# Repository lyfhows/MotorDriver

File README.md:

# L298N Dual Motor Driver with Power Monitoring

A custom KiCad PCB built around the **L298N** dual H-bridge. It improves on the common red L298N module with Schottky flyback diodes, reverse-polarity and surge protection, an onboard logic supply, voltage / current / power monitoring over I2C, and a hardware overcurrent limit that works without firmware.

---

## Features

- Drives **two independent brushed DC motors** (or one motor with both channels paralleled)
- **Schottky flyback diodes** (SS36) on all four outputs, instead of the slow 1N4007s on stock modules
- **Three INA226 monitors** over I2C:
  - supply voltage, total current and power
  - current of motor A
  - current of motor B
- **Hardware overcurrent limit** (LM393 comparators) that cuts the enable lines with no firmware involved
- **Input protection:** fuse, reverse-polarity P-MOSFET, TVS surge diode and a gate-clamp zener
- **Onboard logic supply:** 5 V buck converter (AP63205) plus a 3.3 V LDO
- **3.3 V or 5 V logic** selectable with a solder jumper, so it works with ESP32 / Pico / STM32 or 5 V Arduino boards
- **Pull-down and series resistors** on all control inputs, so the motors stay off while the MCU is unpowered or booting
- Hand-solderable parts (no BGA, no leadless packages)

## Specifications

| Item | Value |
|---|---|
| Motor driver | L298N, Multiwatt15 |
| Supply voltage | Mostly 12 V or below, designed for up to **24 V** |
| Motor current | 2 A continuous per channel, about 2.5 A repetitive peak, about 4 A total |
| Input path rating | Sized for **5 A** as headroom (fuse 6.3 A). This is not an expected load. |
| Voltage drop | The L298N's bipolar bridge drops roughly 2 to 4 V, so at 12 V a motor sees about 9 V |
| Logic level | 3.3 V or 5 V, set by SJ1 |
| Speed control | PWM on ENA / ENB |
| Direction control | IN1 to IN4 |
| Overcurrent limit | About 2.3 A per channel (adjustable with RV1), hiccup behaviour |
| Monitoring | 3 × INA226 at I2C addresses 0x40, 0x41, 0x42 |
| Board | 110 × 90 mm, 2 layers, 2 oz copper |
| Assembly | Hand soldering |

## Block diagram

```mermaid
flowchart LR
  BAT[Battery] --> F1[Fuse F1]
  F1 --> Q1[Reverse-polarity MOSFET Q1]
  Q1 --> RS1[Shunt RS1 with INA226 U2]
  RS1 --> VS[Motor supply rail VS]
  VS --> U1[L298N U1]
  U1 --> MA[Motor A]
  U1 --> MB[Motor B]
  VS --> U3[5 V buck U3]
  U3 --> U5[3.3 V LDO U5]
  U3 --> SJ1[Logic rail selector SJ1]
  U5 --> SJ1
  SJ1 --> MON[INA226s, LM393, I2C pull-ups]
  U1 -- SENSE pins --> SH[Shunts RSA and RSB]
  SH --> I6[INA226 U6 and U7]
  SH --> CMP[LM393 comparator U4]
  CMP -- pulls enable low --> U1
  MCU[Microcontroller] -- PWM and direction --> U1
  MCU <-- I2C --> MON
```

## How it works

### Power path
Battery positive goes through the fuse (F1) and the P-channel MOSFET (Q1), which blocks reverse polarity. It then passes through the 15 mΩ shunt (RS1), which the first INA226 (U2) measures, and arrives at the motor supply rail. The TVS diode (D11) and 470 µF bulk capacitor (C1) sit on that rail, which feeds the L298N's VS pin and the buck converter.

### Logic power
The AP63205 buck converter makes 5 V from the supply rail. A 3.3 V LDO (AP2112K-3.3) follows it. The solder jumper **SJ1** chooses which of the two feeds the "logic rail", which powers the INA226s, the LM393 and the I2C pull-ups. Bridge it to match your microcontroller's logic level. The L298N's logic supply pin always runs from 5 V.

### Current monitoring
- **U2** measures the total current drawn from the supply across the 15 mΩ shunt RS1, plus the supply voltage and power.
- **U6** and **U7** measure each motor's current across a 33 mΩ shunt (RSA, RSB) connected to the L298N's SENSE pins.
- Each INA226 has 10 Ω input filter resistors and a 100 nF capacitor across its inputs.

### Hardware overcurrent limit
Each SENSE voltage also goes through a 1 kΩ / 100 nF filter to a comparator in the LM393 (U4). A trimmer (RV1) sets the reference to about 75 mV, which is roughly 2.3 A on a 33 mΩ shunt. When the current exceeds that, the comparator's open-collector output pulls the matching enable line low through a BAT54J Schottky diode, and the motor current falls. The limit is **not latched**: the motor restarts when the current drops, so a stalled motor pulses on and off.

### Input protection for control lines
IN1 to IN4 have 100 Ω series resistors and 10 kΩ pull-downs. ENA and ENB have 2.2 kΩ series resistors and 22 kΩ pull-downs. With the MCU off or disconnected, the bridge stays disabled.

## Bill of materials

**ICs and semiconductors**

| Ref | Part | Footprint |
|---|---|---|
| U1 | L298N (Multiwatt15) | `Package_TO_SOT_THT:TO-220-15_P2.54x2.54mm_StaggerOdd_Lead4.58mm_Vertical` |
| U2, U6, U7 | INA226AIDGSR | `Package_SO:VSSOP-10_3x3mm_P0.5mm` |
| U3 | AP63205WU-7 (5 V buck) | `Package_TO_SOT_SMD:TSOT-23-6` |
| U4 | LM393 (dual comparator) | `Package_SO:SOIC-8_3.9x4.9mm_P1.27mm` |
| U5 | AP2112K-3.3 (3.3 V LDO) | `Package_TO_SOT_SMD:SOT-23-5` |
| Q1 | P-MOSFET, 40 V, at least 10 A (e.g. AOD4185) | `Package_TO_SOT_SMD:TO-252-2` |
| D1 to D8 | SS36 (60 V, 3 A Schottky) | `Diode_SMD:D_SMA` |
| D9 | LED, green (power) | `LED_SMD:LED_0805_2012Metric` |
| D10 | BZT52B15 (15 V zener) | `Diode_SMD:D_SOD-123F` |
| D11 | SMAJ28A (unidirectional TVS) | `Diode_SMD:D_SMA` |
| D12, D13 | BAT54J (Schottky) | `Diode_SMD:D_SOD-323F` |

**Resistors** (0603 unless noted)

| Ref | Value | Purpose |
|---|---|---|
| R1 to R4 | 10 kΩ | Pull-downs on IN1 to IN4 |
| R5, R6 | 22 kΩ | Pull-downs on ENA / ENB |
| R7, R8 | 2.2 kΩ | Series on ENA / ENB |
| R9 | 10 kΩ | Q1 gate to GND |
| R10, R11 | 4.7 kΩ | SDA / SCL pull-ups |
| R12 | 10 kΩ | ALERT pull-up |
| R13 | 1 kΩ | Power LED |
| R14 | 47 kΩ | Comparator reference, top |
| R15, R16 | 1 kΩ | Comparator input filters |
| R17 | 100 kΩ | Buck EN pull-up |
| R18 to R21 | 100 Ω | Series on IN1 to IN4 |
| R22 to R27 | 10 Ω | INA226 input filters |
| RS1 | 15 mΩ, 1 W, 1%, 2512 | Supply shunt |
| RSA, RSB | 33 mΩ, 1 W, 1%, 2512 | Motor shunts |
| RV1 | 2 kΩ multiturn trimmer | Trip threshold (Bourns 3296W) |

**Capacitors**

| Ref | Value | Footprint |
|---|---|---|
| C1 | 470 µF, 50 V electrolytic | `Capacitor_THT:CP_Radial_D10.0mm_P5.00mm` |
| C5 | 10 µF, 50 V | `Capacitor_SMD:C_1206_3216Metric` |
| C6 | 22 µF, 16 V | `Capacitor_SMD:C_1206_3216Metric` |
| C8 | 1 µF | `Capacitor_SMD:C_0805_2012Metric` |
| C9 | 2.2 µF | `Capacitor_SMD:C_0805_2012Metric` |
| C2 to C4, C7, C10 to C18 | 100 nF, 50 V X7R | `Capacitor_SMD:C_0805_2012Metric` |

Ceramic capacitors lose capacitance under DC bias, so keep C5 and C6 in 1206 or larger.

**Other parts**

| Ref | Part | Notes |
|---|---|---|
| L1 | 4.7 µH shielded inductor, saturation current 3 A or more | The AP63205 datasheet recommends 4.7 µH for a 5 V output. Confirm against your datasheet. |
| F1 | 6.3 A fast-blow fuse, 5×20 mm, with PCB holder | |
| SJ1 | 3-pad solder jumper | Selects 5 V or 3.3 V logic |
| JP1, JP2 | 2-pad solder jumpers, bridged | Disconnect the I2C pull-ups if needed |
| J1 to J3 | 2-pin 5.08 mm screw terminals | Battery, motor A, motor B |
| J4 | 1×7 pin header | Control inputs |
| J5 | 1×5 pin header | I2C and alert |
| H1 to H4 | M3 mounting holes | Unplated, no electrical connection |
| TP1 to TP8 | Test points | |
| HS1 | Heatsink with thermal pad | Not on the PCB. Mounts on the L298N tab. |

**Totals:** 80 components, or 92 footprints including the mounting holes and test points. You also need to buy the fuse, the heatsink and an M3 screw for the L298N tab.

## Connector pinouts

| Connector | Pin | Signal |
|---|---|---|
| **J1** battery | 1 | Battery positive |
| | 2 | GND |
| **J2** motor A | 1, 2 | OUT1, OUT2 |
| **J3** motor B | 1, 2 | OUT3, OUT4 |
| **J4** control | 1 | ENA |
| | 2 to 5 | IN1, IN2, IN3, IN4 |
| | 6 | ENB |
| | 7 | GND |
| **J5** I2C | 1 | SDA |
| | 2 | SCL |
| | 3 | ALERT |
| | 4 | Logic rail output (3.3 V or 5 V, as set by SJ1) |
| | 5 | GND |

**SJ1:** pin 1 is +5 V, pin 3 is +3.3 V, and pin 2 (the centre pad) is the logic rail. Solder-bridge pins 1 and 2 for 5 V logic, or pins 2 and 3 for 3.3 V logic. Never bridge all three. Don't back-feed the logic rail from the MCU.

### L298N pin connections

| Pin | Signal |
|---|---|
| 1 | SENSE_A (to RSA, then GND) |
| 2, 3 | OUT1, OUT2 |
| 4 | VS (motor supply) |
| 5, 7 | IN1, IN2 |
| 6 | ENA |
| 8 | GND (the metal tab is also GND) |
| 9 | VSS (+5 V logic) |
| 10, 12 | IN3, IN4 |
| 11 | ENB |
| 13, 14 | OUT3, OUT4 |
| 15 | SENSE_B (to RSB, then GND) |

**Flyback diodes:** D1, D2, D5 and D6 go from OUT1, OUT2, OUT3 and OUT4 up to VS (anode on the output). D3, D4, D7 and D8 go from GND to OUT1, OUT2, OUT3 and OUT4 (anode on GND).

### INA226 pin connections (VSSOP-10)

| Pin | Name | U2 (supply, 0x40) | U6 (motor A, 0x41) | U7 (motor B, 0x42) |
|---|---|---|---|---|
| 1 | A1 | GND | GND | GND |
| 2 | A0 | GND | Logic rail | SDA |
| 3 | ALERT | ALERT | ALERT | ALERT |
| 4 | SDA | SDA | SDA | SDA |
| 5 | SCL | SCL | SCL | SCL |
| 6 | VS | Logic rail | Logic rail | Logic rail |
| 7 | GND | GND | GND | GND |
| 8 | VBUS | Motor supply rail | Same net as pin 9 | Same net as pin 9 |
| 9 | VIN− | Via R23 to the load side of RS1 | Via R25 to RSA's ground end | Via R27 to RSB's ground end |
| 10 | VIN+ | Via R22 to the battery side of RS1 | Via R24 to the SENSE_A pin | Via R26 to the SENSE_B pin |

The bus-voltage reading on U6 and U7 is meaningless (they see only millivolts), so ignore it.

## Schematic Layout

## PCB layout

## PCB 3D view

### Layout rules used

| Item | Value |
|---|---|
| Copper | 2 oz, 2 layers |
| Power tracks (VS, GND) | 2 mm or wider, or copper pours |
| Motor output tracks | 1.5 mm or wider |
| Signal tracks | 0.25 to 0.3 mm |
| Clearance | 0.3 mm or more (check your fab's minimum) |
| Part spacing | About 2 mm, for hand soldering |
| Mounting holes | 5 mm copper-free clearance |

## Bring-up procedure

1. **Check for shorts** with a multimeter (VS to GND, +5 V to GND) before applying power.
2. **Populate the power section first:** fuse, Q1, RS1, the buck and the LDO. Power it from a **current-limited bench supply** at about 12 V with the limit near 0.2 A. Confirm +5 V and +3.3 V.
3. **Solder jumper:** bridge SJ1 to match your MCU.
4. **Add the L298N and diodes.** Test with no motor, then a small motor at low PWM.
5. **Add the INA226s one at a time,** scan the I2C bus, and compare the readings against a multimeter.
6. **Set the overcurrent trimmer last:** adjust RV1 while measuring the reference voltage (about 75 mV).

## Firmware notes

### I2C addresses

| Device | Address | Measures |
|---|---|---|
| U2 | 0x40 | Supply voltage, total current, power |
| U6 | 0x41 | Motor A current |
| U7 | 0x42 | Motor B current |

### Calibration

The INA226 calibration register value is `CAL = 0.00512 / (Current_LSB × R_shunt)`.

| Chip | Shunt | Current_LSB | CAL | Full-scale |
|---|---|---|---|---|
| U2 | 15 mΩ | 1 mA | 341 | About 5.4 A |
| U6, U7 | 33 mΩ | 0.5 mA | 310 | About 2.48 A (readings saturate here) |

The power register's LSB is 25 times the Current_LSB. The bus voltage LSB is 1.25 mV.

### Minimal example (Arduino-style)

```cpp
#include <Wire.h>

const uint8_t INA_SUPPLY  = 0x40;
const uint8_t INA_MOTOR_A = 0x41;
const uint8_t INA_MOTOR_B = 0x42;

void writeReg(uint8_t addr, uint8_t reg, uint16_t val) {
  Wire.beginTransmission(addr);
  Wire.write(reg);
  Wire.write(val >> 8);
  Wire.write(val & 0xFF);
  Wire.endTransmission();
}

int16_t readReg(uint8_t addr, uint8_t reg) {
  Wire.beginTransmission(addr);
  Wire.write(reg);
  Wire.endTransmission(false);
  Wire.requestFrom(addr, (uint8_t)2);
  return (Wire.read() << 8) | Wire.read();
}

void setup() {
  Serial.begin(115200);
  Wire.begin();
  // Configuration register (0x00): 64 averages, 1.1 ms conversion time
  writeReg(INA_SUPPLY,  0x00, 0x4727);
  writeReg(INA_MOTOR_A, 0x00, 0x4727);
  writeReg(INA_MOTOR_B, 0x00, 0x4727);
  // Calibration register (0x05)
  writeReg(INA_SUPPLY,  0x05, 341);
  writeReg(INA_MOTOR_A, 0x05, 310);
  writeReg(INA_MOTOR_B, 0x05, 310);
}

void loop() {
  float busV   = readReg(INA_SUPPLY, 0x02) * 1.25 / 1000.0;  // volts
  float supplyA = readReg(INA_SUPPLY,  0x04) * 1.0 / 1000.0; // amps
  float motorA  = readReg(INA_MOTOR_A, 0x04) * 0.5 / 1000.0; // amps
  float motorB  = readReg(INA_MOTOR_B, 0x04) * 0.5 / 1000.0; // amps
  Serial.printf("V=%.2f  I_total=%.3f  I_A=%.3f  I_B=%.3f\n",
                busV, supplyA, motorA, motorB);
  delay(200);
}
```

Set the undervoltage alert limit in U2's mask/enable and alert-limit registers to suit your battery chemistry.

## Known limitations

- **The L298N can't deliver 5 A.** The 5 A figure only sizes the input path. Real limits are 2 A per channel and about 4 A in total.
- **Voltage drop:** the L298N's bipolar bridge drops roughly 2 to 4 V, and at full load it dissipates several watts and needs a heatsink (about 3 °C/W or better for continuous use).
- **Overcurrent limit is a hiccup, not a latch.** A stalled motor pulses on and off, and the MCU isn't told when it trips.
- **No short-circuit protection on the motor outputs** beyond the fuse and the hiccup limit. The L298N has no fault flag.
- **Per-motor current readings under PWM** reflect only the on-time current. The motor's freewheeling current flows through the flyback diodes and doesn't pass the shunt, so the reading is lower than the smoothed motor current. Treat it as a trend or overload indicator.
- **INA226 bus voltage rating:** VBUS has a 40 V absolute maximum. The SMAJ28A TVS clamps at about 45 V at its full surge current, so only an extreme surge could exceed it. For a supply near 24 V, consider the SMAJ26A instead.
- **No isolation** between the motor side and the logic side. They share one ground.
- **No onboard temperature sensing or fan control.**
- **Hardest part to hand-solder:** the three VSSOP-10 INA226 chips.
- **Not yet built or tested.**

## Design decisions

| Decision | Choice |
|---|---|
| Driver IC | Keep the L298N (not replaced by a MOSFET bridge) |
| Flyback diodes | Schottky SS36 instead of 1N4007 |
| Logic-side isolation | None. Series and pull-down resistors only. |
| Overcurrent protection | Comparator hiccup limit, no latch |
| Temperature sensor and fan | Left out to keep the board simple |
| Per-motor monitoring | Kept (one INA226 per motor) |
| Analog hardware P-loop | Not included. Closed-loop control is left to firmware. |

## License

MIT License

## Author

Abhinav Pentyala

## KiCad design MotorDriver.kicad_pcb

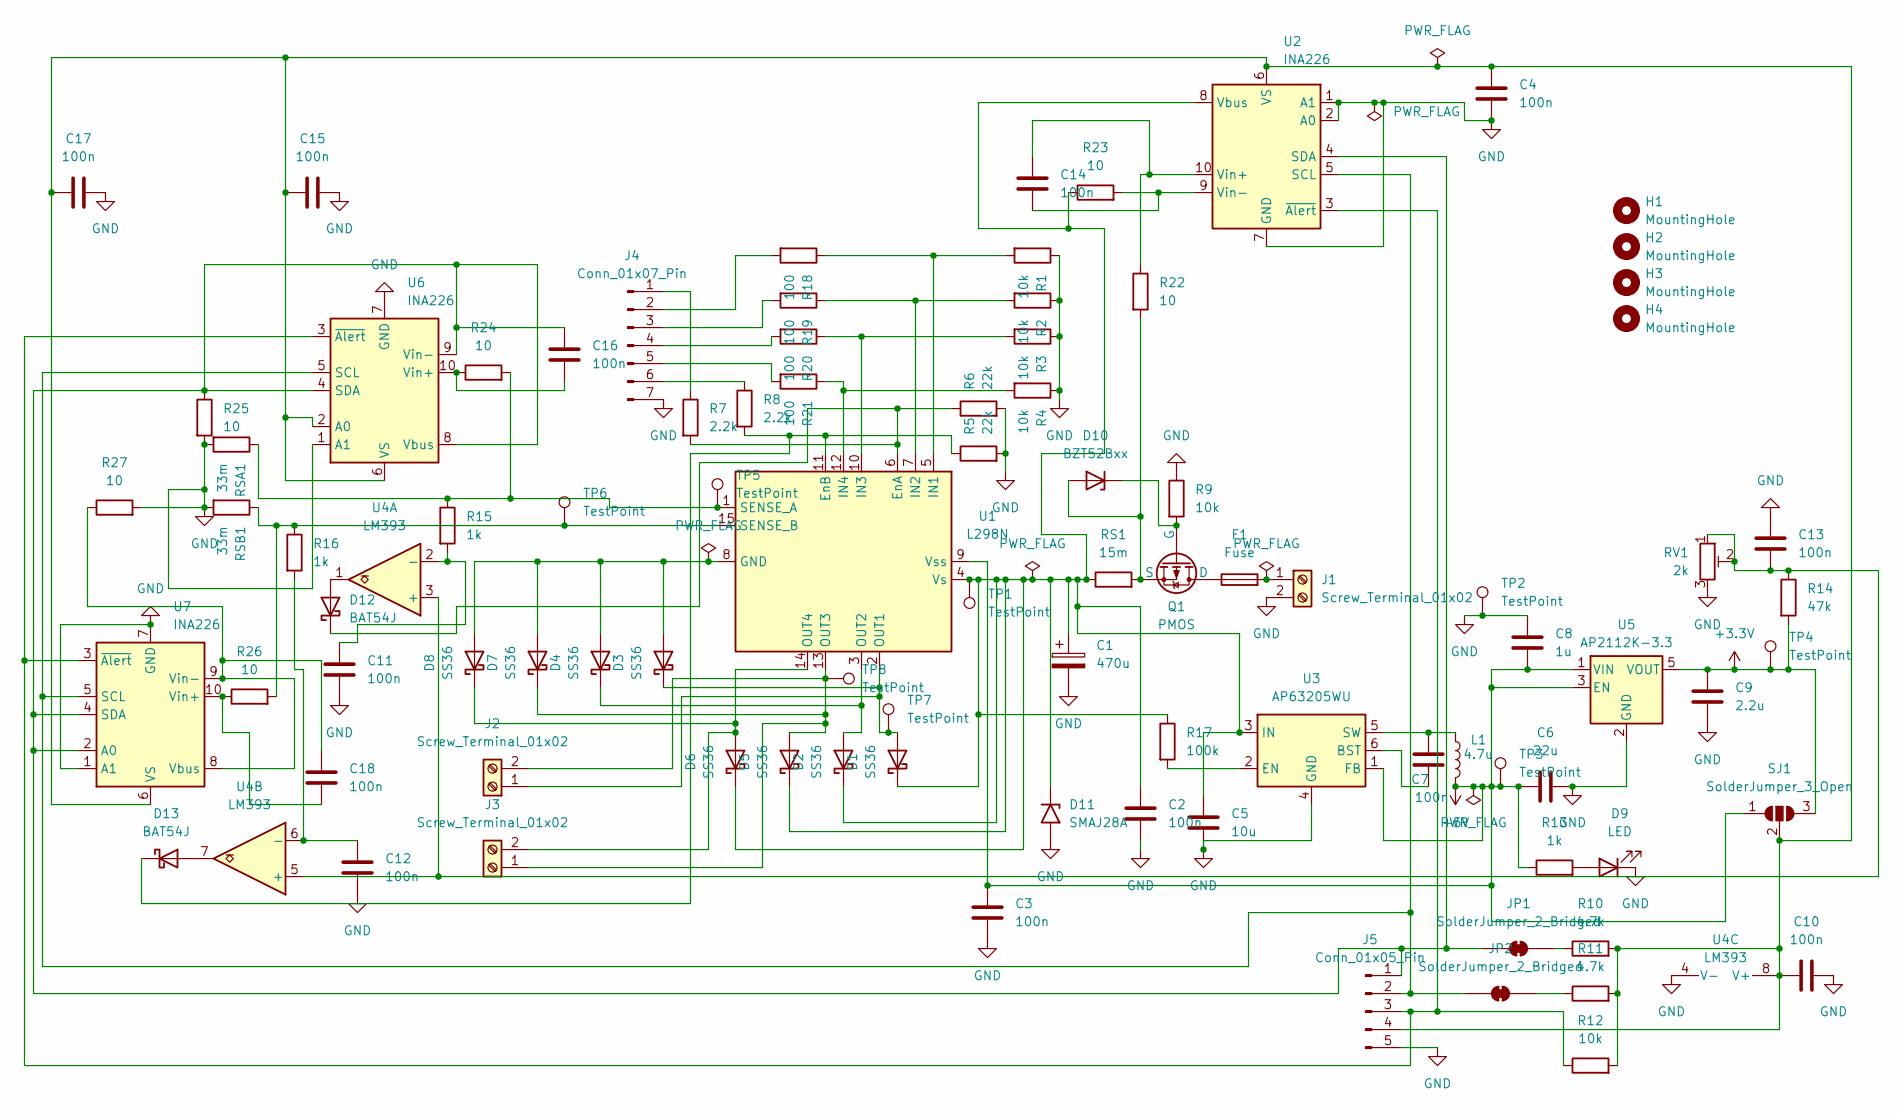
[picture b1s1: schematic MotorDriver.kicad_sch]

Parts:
C1: 470u; CP_Radial_D10.0mm_P5.00mm_P7.50mm
C2, C3, C4, C7, C10, C11, C12, C13, C14, C15, C16, C17, C18: 100n; C_0805_2012Metric_Pad1.18x1.45mm_HandSolder
C5: 10u; C_1206_3216Metric_Pad1.33x1.80mm_HandSolder
C6: 22u; C_1206_3216Metric_Pad1.33x1.80mm_HandSolder
C8: 1u; C_0805_2012Metric_Pad1.18x1.45mm_HandSolder
C9: 2.2u; C_0805_2012Metric_Pad1.18x1.45mm_HandSolder
D1, D2, D3, D4, D5, D6, D7, D8: SS36; D_SMA
D9: LED; LED_0805_2012Metric_Pad1.15x1.40mm_HandSolder
D10: BZT52Bxx; D_SOD-123F
D11: SMAJ28A; D_SMA
D12, D13: BAT54J; D_SOD-323F
F1: Fuse; Fuseholder_Cylinder-5x20mm_Schurter_0031_8201_Horizontal_Op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
H1, H2, H3, H4: MountingHole; MountingHole_3.2mm_M3
J1, J2, J3: Screw_Terminal_01x02; TerminalBlock_Phoenix_MKDS-1,5-2-5.08_1x02_P5.08mm_Horizont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
J4: Conn_01x07_Pin; PinHeader_1x07_P2.54mm_Vertical
J5: Conn_01x05_Pin; PinHeader_1x05_P2.54mm_Vertical
JP1, JP2: SolderJumper_2_Bridged; SolderJumper-2_P1.3mm_Bridged_RoundedPad1.0x1.5mm
L1: 4.7u; L_Bourns_SRN6045TA
Q1: PMOS; TO-252-2
R1, R2, R3, R4, R9, R12: 10k; R_0603_1608Metric_Pad0.98x0.95mm_HandSolder
R5, R6: 22k; R_0603_1608Metric_Pad0.98x0.95mm_HandSolder
R7, R8: 2.2k; R_0603_1608Metric_Pad0.98x0.95mm_HandSolder
R10, R11: 4.7k; R_0603_1608Metric_Pad0.98x0.95mm_HandSolder
R13, R15, R16: 1k; R_0603_1608Metric_Pad0.98x0.95mm_HandSolder
R14: 47k; R_0603_1608Metric_Pad0.98x0.95mm_HandSolder
R17: 100k; R_0603_1608Metric_Pad0.98x0.95mm_HandSolder
R18, R19, R20, R21: 100; R_0603_1608Metric_Pad0.98x0.95mm_HandSolder
R22, R23, R24, R25, R26, R27: 10; R_0603_1608Metric_Pad0.98x0.95mm_HandSolder
RS1: 15m; R_2512_6332Metric_Pad1.40x3.35mm_HandSolder
RSA1: 33m; R_2512_6332Metric_Pad1.40x3.35mm_HandSolder
RSB1: 33m; R_2512_6332Metric_Pad1.40x3.35mm_HandSolder
RV1: 2k; Potentiometer_Bourns_3296W_Vertical
SJ1: SolderJumper_3_Open; SolderJumper-3_P1.3mm_Open_RoundedPad1.0x1.5mm
TP1, TP2, TP3, TP4, TP5, TP6, TP7, TP8: TestPoint; TestPoint_Pad_D1.5mm
U1: L298N; TO-220-15_P2.54x5.08mm_StaggerOdd_Lead4.58mm_Vertical
U2, U6, U7: INA226; TSSOP-10_3x3mm_P0.5mm
U3: AP63205WU; TSOT-23-6
U4: LM393; SOIC-8_3.9x4.9mm_P1.27mm
U5: AP2112K-3.3; SOT-23-5

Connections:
+3.3V: C9.1, R14.2, SJ1.3 (B), TP4.1 (1_1), U5.5 (VOUT)
+5V: C3.1, C6.1, C8.2, L1.2, R13.1, SJ1.1 (A), TP3.1 (1_1), U1.9 (Vss), U3.1 (FB), U5.1 (VIN), U5.3 (EN)
GND: C1.2, C2.2, C3.2, C4.2, C5.2, C6.2, C8.1, C9.2, C10.2, C11.2, C12.2, C13.1, C15.2, C17.2, D9.1 (K), D11.2 (A2), J1.2, J4.7, J5.5, R1.1, R2.1, R3.1, R4.1, R5.2, R6.2, R9.1, R25.2, R27.2, RSA1.2, RSB1.2, RV1.3, TP2.1 (1_1), U2.1 (A1), U2.2 (A0), U2.7 (GND), U3.4 (GND), U4.4 (V-), U5.2 (GND), U6.1 (A1), U6.7 (GND), U7.1 (A1), U7.7 (GND)
unnamed: D1.2 (A), D3.1 (K), J2.1, TP7.1 (1_1), U1.2 (OUT1)
unnamed: C1.1, C2.1, C5.1, D1.1 (K), D2.1 (K), D5.1 (K), D6.1 (K), D11.1 (A1), R17.1, R23.1, RS1.1, TP1.1 (1_1), U1.4 (Vs), U2.8 (Vbus), U3.3 (IN)
unnamed: D2.2 (A), D4.1 (K), U1.3 (OUT2)
unnamed: D3.2 (A), D4.2 (A), D7.2 (A), D8.2 (A), U1.8 (GND)
unnamed: D5.2 (A), D7.1 (K), J2.2, J3.1, TP8.1 (1_1), U1.13 (OUT3)
unnamed: D6.2 (A), D8.1 (K), J3.2, U1.14 (OUT4)
unnamed: D9.2 (A), R13.2
unnamed: D10.2 (A), Q1.3 (S), R22.2, RS1.2
unnamed: D10.1 (K), Q1.2 (G), R9.2
unnamed: D12.2 (A), U4.1
unnamed: D12.1 (K), R6.1, R7.2, U1.6 (EnA)
unnamed: D13.2 (A), U4.7
unnamed: D13.1 (K), R5.1, R8.2, U1.11 (EnB)
unnamed: F1.2, J1.1
unnamed: J4.1, R7.1
unnamed: J4.2, R18.2
unnamed: J4.3, R19.2
unnamed: J4.4, R20.2
unnamed: J4.5, R21.2
unnamed: J4.6, R8.1
unnamed: C16.1, J5.1, JP1.1 (A), R25.1, U2.4 (SDA), U6.4 (SDA), U6.8 (Vbus), U6.9 (Vin-), U7.2 (A0), U7.4 (SDA)
unnamed: J5.2, JP2.1 (A), U2.5 (SCL), U6.5 (SCL), U7.5 (SCL)
unnamed: J5.3, R12.1, U2.3 (~Alert), U6.3 (~Alert), U7.3 (~Alert)
unnamed: C4.1, C10.1, C15.1, C17.1, J5.4, R10.2, R11.2, R12.2, SJ1.2 (C), U2.6 (VS), U4.8 (V+), U6.2 (A0), U6.6 (VS), U7.6 (VS)
unnamed: JP1.2 (B), R10.1
unnamed: JP2.2 (B), R11.1
unnamed: F1.1, Q1.1 (D)
unnamed: R1.2, R18.1, U1.5 (IN1)
unnamed: R2.2, R19.1, U1.7 (IN2)
unnamed: R3.2, R20.1, U1.10 (IN3)
unnamed: R4.2, R21.1, U1.12 (IN4)
unnamed: R15.1, R24.2, RSA1.1, TP5.1 (1_1), U1.1 (SENSE_A)
unnamed: R16.1, R26.2, RSB1.1, TP6.1 (1_1), U1.15 (SENSE_B)
unnamed: C14.1, R22.1, U2.10 (Vin+)
unnamed: C14.2, R23.2, U2.9 (Vin-)
unnamed: C7.2, U3.6 (BST)
unnamed: R17.2, U3.2 (EN)
unnamed: C7.1, L1.1, U3.5 (SW)
unnamed: C13.2, R14.1, RV1.1, RV1.2, U4.3 (+), U4.5 (+)
unnamed: C11.1, R15.2, U4.2 (-)
unnamed: C12.1, R16.2, U4.6 (-)
unnamed: C16.2, R24.1, U6.10 (Vin+)
unnamed: C18.1, R27.1, U7.8 (Vbus), U7.9 (Vin-)
unnamed: C18.2, R26.1, U7.10 (Vin+)

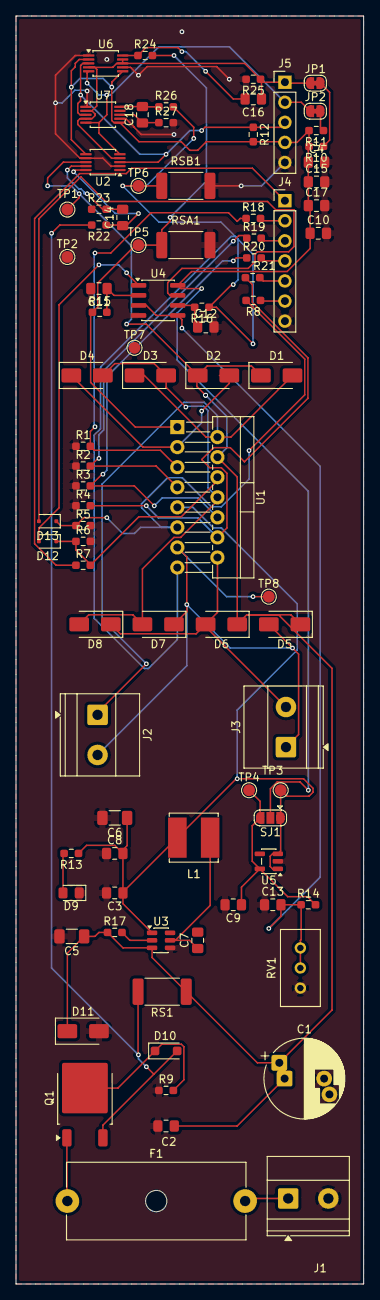
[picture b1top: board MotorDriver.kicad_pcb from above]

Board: 2 copper layers, 44.0 x 160.5 mm, 88 parts (0 on the bottom side), 47 nets.

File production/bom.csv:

Designator,Footprint,Quantity,Value,LCSC Part #
C1,CP_Radial_D10.0mm_P5.00mm_P7.50mm,1,470u,
"C10, C11, C12, C13, C14, C15, C16, C17, C18, C2, C3, C4, C7",0805,13,100n,
C5,1206,1,10u,
C6,1206,1,22u,
C8,0805,1,1u,
C9,0805,1,2.2u,
"D1, D2, D3, D4, D5, D6, D7, D8",D_SMA,8,SS36,
D10,D_SOD-123F,1,BZT52Bxx,
D11,D_SMA,1,SMAJ28A,
"D12, D13",D_SOD-323F,2,BAT54J,
D9,0805,1,LED,
F1,Fuseholder_Cylinder-5x20mm_Schurter_0031_8201_Horizontal_Open,1,Fuse,
"J1, J2, J3","TerminalBlock_Phoenix_MKDS-1,5-2-5.08_1x02_P5.08mm_Horizontal",3,Screw_Terminal_01x02,
J4,PinHeader_1x07_P2.54mm_Vertical,1,Conn_01x07_Pin,
J5,PinHeader_1x05_P2.54mm_Vertical,1,Conn_01x05_Pin,
L1,L_Bourns_SRN6045TA,1,4.7u,
Q1,TO-252-2,1,PMOS,
"R1, R12, R2, R3, R4, R9",0603,6,10k,
"R10, R11",0603,2,4.7k,
"R13, R15, R16",0603,3,1k,
R14,0603,1,47k,
R17,0603,1,100k,
"R18, R19, R20, R21",0603,4,100,
"R22, R23, R24, R25, R26, R27",0603,6,10,
"R5, R6",0603,2,22k,
"R7, R8",0603,2,2.2k,
RS1,2512,1,15m,
"RSA1, RSB1",2512,2,33m,
RV1,Potentiometer_Bourns_3296W_Vertical,1,2k,
"TP1, TP2, TP3, TP4, TP5, TP6, TP7, TP8",TestPoint_Pad_D1.5mm,8,TestPoint,
U1,TO-220-15_P2.54x5.08mm_StaggerOdd_Lead4.58mm_Vertical,1,L298N,
"U2, U6, U7",TSSOP-10_3x3mm_P0.5mm,3,INA226,
U3,TSOT-23-6,1,AP63205WU,
U4,SOIC-8_3.9x4.9mm_P1.27mm,1,LM393,
U5,SOT-23-5,1,AP2112K-3.3,
